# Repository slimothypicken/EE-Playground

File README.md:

# Hardware Learning Lab – PCB Design & Signal Analysis Projects

This repository is a collection of hands-on hardware projects focused on learning practical PCB design and signal analysis. It documents the full workflow from initial schematics and simulations through PCB layout, fabrication files, bring-up notes, and measurement results for each project. The goal is to build intuition for real-world behavior—parasitics, noise, grounding, and signal integrity—rather than just producing “perfect” textbook circuits.

Each project includes design files, brief writeups of design decisions, test setups, and lessons learned so that others can follow along, replicate the work, or adapt the designs for their own experiments. Over time, this lab will expand to cover topics like analog front-ends, microcontroller boards, filtering, and basic high-speed signal considerations, forming a growing reference for self-directed hardware learners.

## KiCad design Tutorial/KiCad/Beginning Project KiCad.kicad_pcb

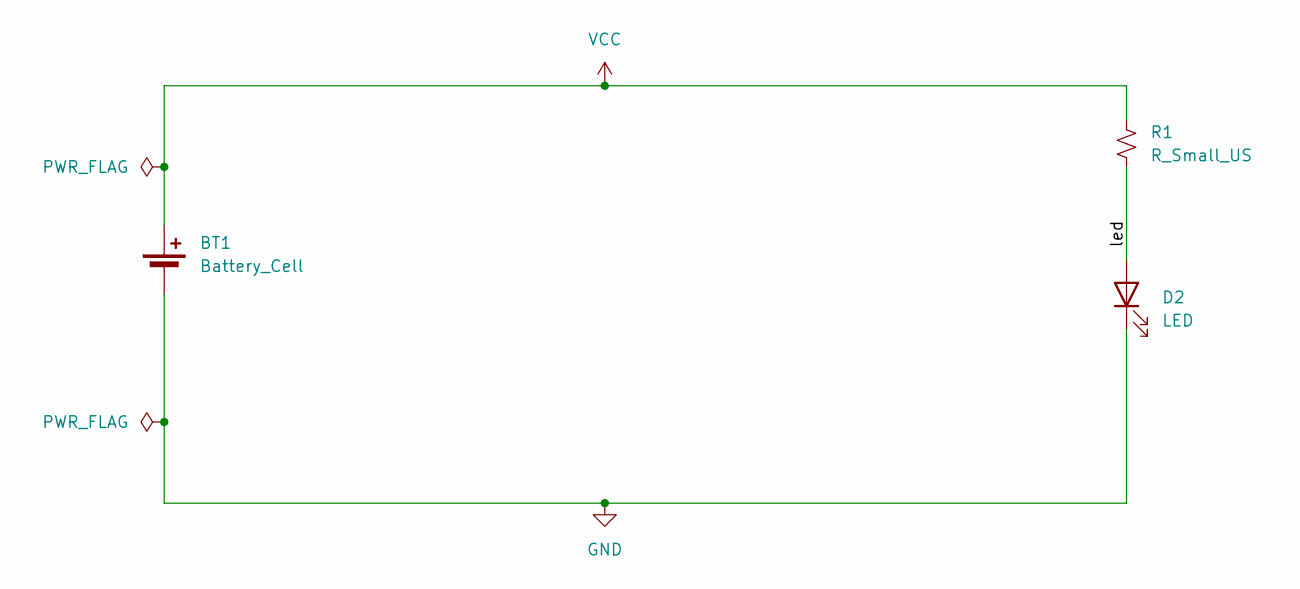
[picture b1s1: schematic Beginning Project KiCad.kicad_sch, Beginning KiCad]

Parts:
BT1: Battery_Cell; BatteryHolder_Keystone_1058_1x2032
D2: LED; LED_D3.0mm
R1: R_Small_US; R_Axial_DIN0309_L9.0mm_D3.2mm_P12.70mm_Horizontal

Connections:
/led: D2.2 (A), R1.2
GND: BT1.2 (-), D2.1 (K)
VCC: BT1.1 (+), R1.1

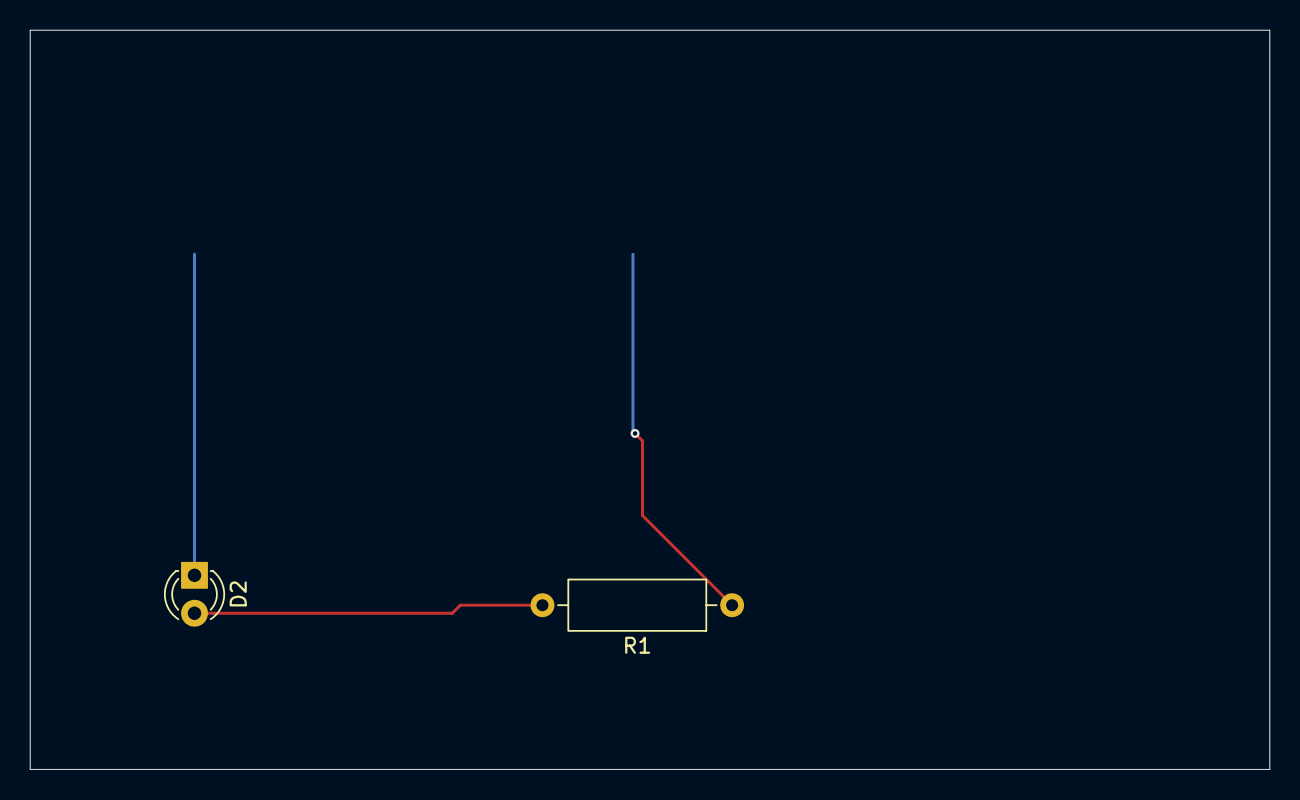
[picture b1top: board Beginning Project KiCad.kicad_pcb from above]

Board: 2 copper layers, 83.0 x 49.5 mm, 3 parts (1 on the bottom side), 3 nets.

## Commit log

2026-01-18 Created first board
    This tutorial covers Part 3 of the KiCad part 3 tutorial which gives me a chance to play around with the setting of copper zones, Design Rule Checking, routing tracks, and placing symbols from the pr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
2026-01-19 Completion of Tutorial of KiCad
    I completed the tutorial. One part that tripped me up was clicking the footprint editor before the symbol editor. Once that was resolved, the rest of the tutorial flowed easily. If people have other 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
2026-01-19 Completion of Tutorial
    I completed the tutorial. One part that tripped me up was clicking the footprint editor before the symbol editor. Once that was resolved, the rest of the tutorial flowed easily. If people have other 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
2026-01-19 Create Symbol Creation
2026-01-19 Create File
2026-01-19 Create Symbols
2026-01-19 Completion of Tutuorial
    I completed the tutorial. One part that tripped me up was clicking the footprint editor before the symbol editor. Once that was resolved, the rest of the tutorial flowed easily. If people have other 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
2026-01-19 Create Tutorial Complete
2026-01-19 Tutorial Completion
    I completed the tutorial. One part that tripped me up was clicking the footprint editor before the symbol editor. Once that was resolved, the rest of the tutorial flowed easily. If people have other 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
2026-01-20 Create commit
2026-01-20 Added Signal Analysis projects
    Getting familiar with the file handler system as well as serial logging to ensure data can be properly read as well as logged somewhere by a user. This version is for virtual hardware.
